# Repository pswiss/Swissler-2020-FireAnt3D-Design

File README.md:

# Swissler-2020-FireAnt3D-Design

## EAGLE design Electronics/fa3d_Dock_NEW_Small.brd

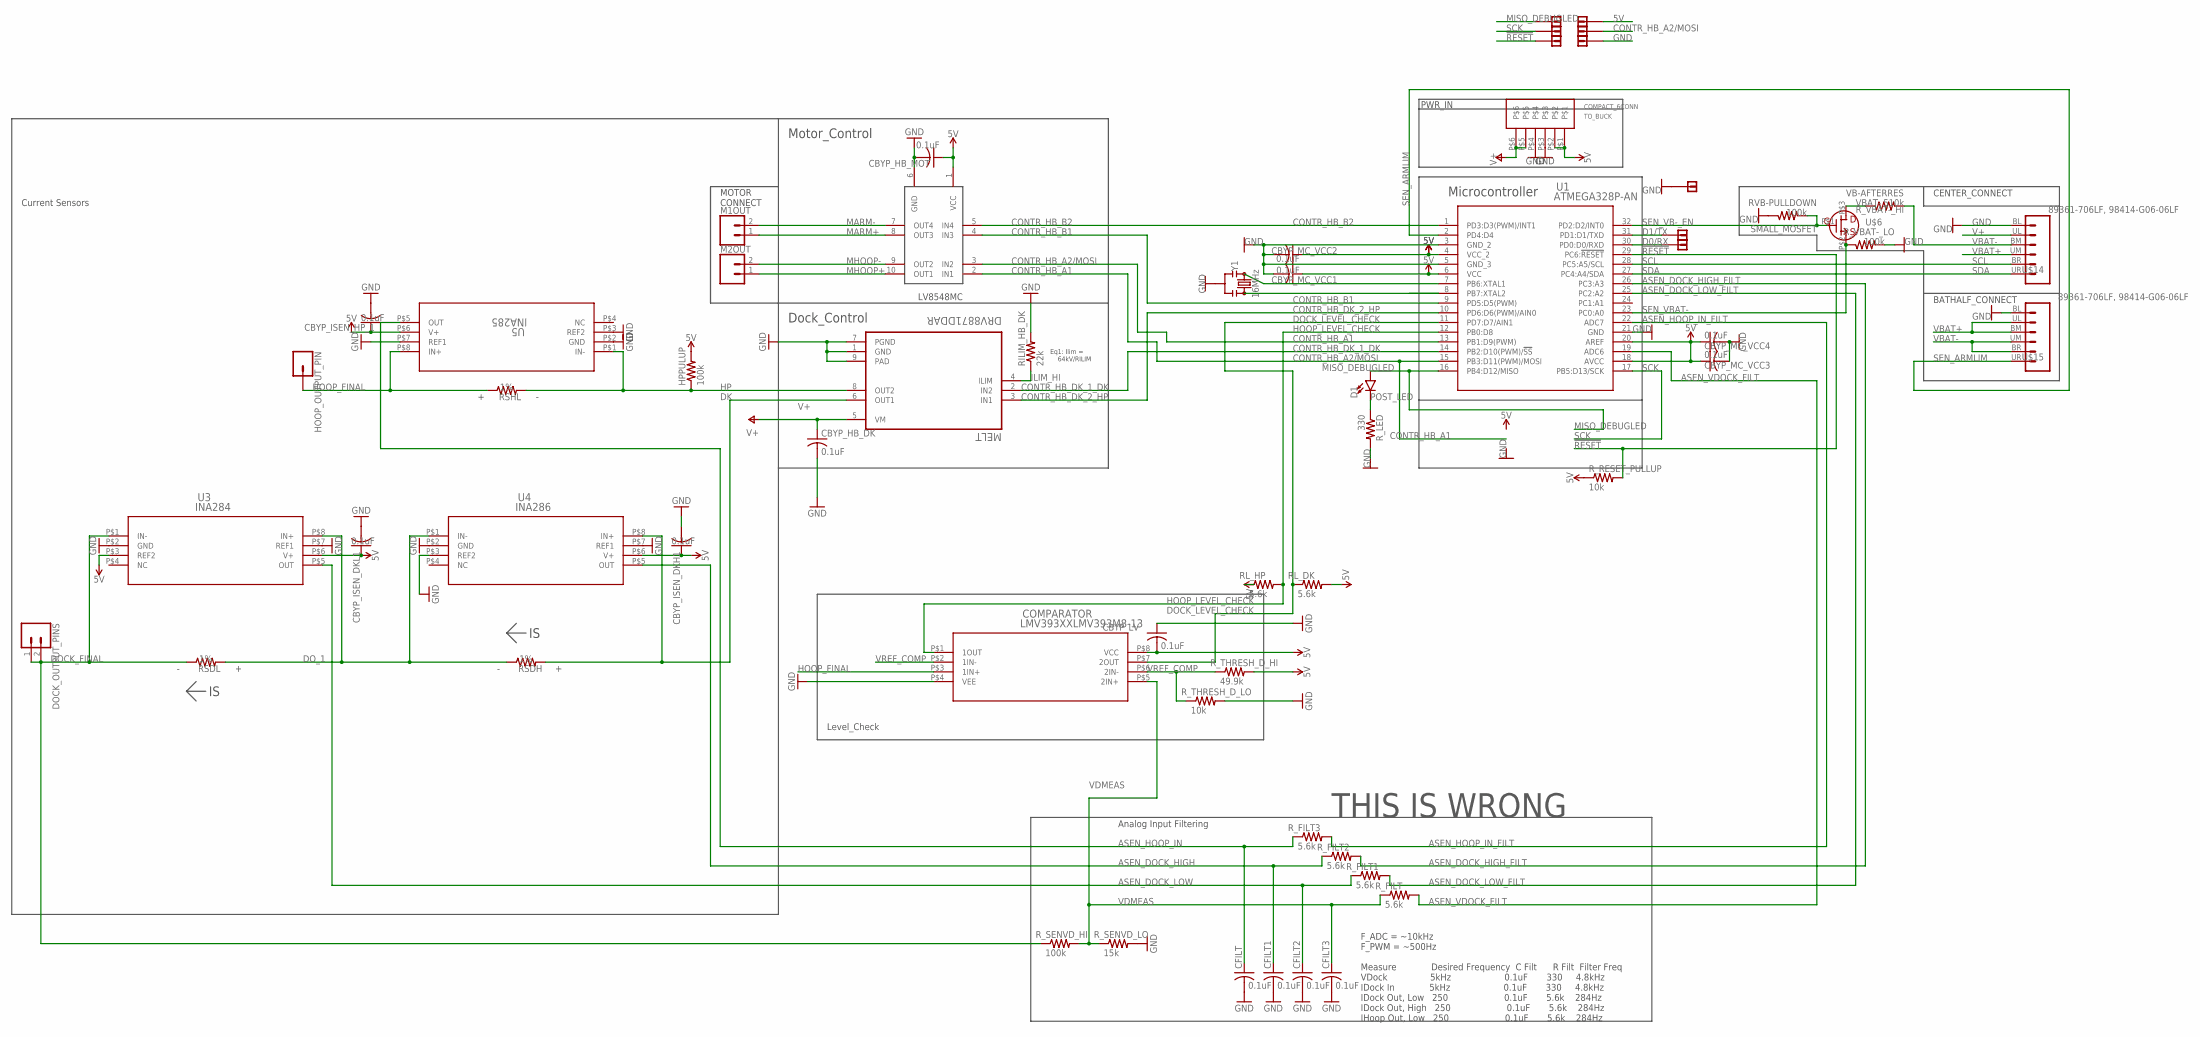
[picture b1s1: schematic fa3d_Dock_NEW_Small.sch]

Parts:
CBYP_HB_DK: 0.1uF; C0603; PARTNO CL10B104KB8NNNC
CBYP_HB_MOT: 0.1uF; C0402; PARTNO 885012105010
CBYP_ISEN_DKH1: 0.1uF; C0402; PARTNO 885012105010
CBYP_ISEN_DKL1: 0.1uF; C0402; PARTNO 885012105010
CBYP_ISEN_HP_1: 0.1uF; C0402; PARTNO 885012105010
CBYP_LV: 0.1uF; C0402; PARTNO 885012105010
CBYP_MC_VCC1, CBYP_MC_VCC2, CBYP_MC_VCC3, CBYP_MC_VCC4: 0.1uF; C0402; PARTNO 885012105010
CFILT, CFILT1, CFILT2, CFILT3: 0.1uF; C0402; PARTNO 885012105010
COMPARATOR: LMV393XXLMV393M8-13; MSOP-8; PARTNO LMV393M8-13
D1: LED0603; LED-0603; PARTNO SML-D12U1WT86
DOCK_OUTPUT_PINS: CONN_02; 1X02
HOOP_OUTPUT_PIN: CONN_01; 1X01
HPPULUP: 100k; R0402; PARTNO RMCF0402JT100K
M1OUT, M2OUT: CONN_02; 1X02
MELT: DRV8871DDAR; SOIC127P600X170-8N; PARTNO DRV8871DDAR
MOTOR: LV8548MC-AH; 10-SOP; PARTNO LV8548MC-AH
RILIM_HB_DK: 22k; R0603; PARTNO RMCF0402JT22K0
RL_DK: 5.6k; R0402; PARTNO CRGCQ0402F5K6
RL_HP: 5.6k; R0402; PARTNO CRGCQ0402F5K6
RSDH: 25m; R0603; PARTNO ERJ-3BWFR025V
RSDL: 25m; R0603; PARTNO ERJ-3BWFR025V
RSHL: 25m; R0603; PARTNO ERJ-3BWFR025V
RVB-PULLDOWN: 100k; R0402; PARTNO RMCF0402JT100K
R_FILT, R_FILT1, R_FILT2, R_FILT3: 5.6k; R0402; PARTNO CRGCQ0402F5K6
R_LED: 330; R0402; PARTNO RMCF0402JT330R
R_RESET_PULLUP: 10k; R0402; PARTNO RR0510P-103-D
R_SENVD_HI: 100k; R0402; PARTNO RMCF0402JT100K
R_SENVD_LO: 15k; R0402; PARTNO RMCF0402JT15K0
R_THRESH_D_HI: 49.9k; R0402; PARTNO RMCF0402FT49K9
R_THRESH_D_LO: 10k; R0402; PARTNO RR0510P-103-D
R_VBAT-_HI: 510k; R0402; PARTNO RMCF0402JT510K
R_VBAT-_LO: 100k; R0402; PARTNO RMCF0402JT100K
TO_BUCK: COMPACT_6CONN
U1: ATMEGA328P-AN; 32A; PARTNO ATMEGA328P-AUR
U3: INA284; 8-VSSOP; PARTNO INA284AIDGKR
U4: INA286; 8-VSSOP; PARTNO INA286AIDGKR
U5: INA285; 8-VSSOP; PARTNO INA285AIDGKR
U$1, U$2, U$3, U$4, U$5, U$7, U$8, U$9, U$10: SIMPLE_VIA_CONNECTION; SIMPLEVIA
U$6: SMALL_MOSFET; SOT-23; PARTNO BSS138
U$14, U$15: 89361-706LF, 98414-G06-06LF; 2X3_2MMPITCH; PARTNO 98414-G06-06LF
Y1: 16MHz; RESONATOR-SMD-3.2X1.3; PARTNO CSTNE16M0V530000R0

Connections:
5V: CBYP_HB_MOT.1, CBYP_ISEN_DKH1.1, CBYP_ISEN_DKL1.1, CBYP_ISEN_HP_1.1, CBYP_LV.2, CBYP_MC_VCC1.1, CBYP_MC_VCC2.1, CBYP_MC_VCC3.1, CBYP_MC_VCC4.1, COMPARATOR.P$8 (VCC), HPPULUP.2, MOTOR.1 (VCC), RL_DK.2, RL_HP.1, R_RESET_PULLUP.1, R_THRESH_D_HI.2, TO_BUCK.P$1, TO_BUCK.P$2, U1.4 (VCC_2), U1.6 (VCC), U1.18 (AVCC), U1.20 (AREF), U3.P$3 (REF2), U3.P$6 (V+), U4.P$6 (V+), U5.P$6 (V+), U$10.P$1
!RESET: R_RESET_PULLUP.2, U1.29 (PC6:!RESET), U$7.P$1
ASEN_DOCK_HIGH: CFILT1.1, R_FILT2.1, U4.P$5 (OUT)
ASEN_DOCK_HIGH_FILT: R_FILT2.2, U1.26 (PC3:A3)
ASEN_DOCK_LOW: CFILT2.1, R_FILT1.1, U3.P$5 (OUT)
ASEN_DOCK_LOW_FILT: R_FILT1.2, U1.25 (PC2:A2)
ASEN_HOOP_IN: CFILT.1, R_FILT3.1, U5.P$5 (OUT)
ASEN_HOOP_IN_FILT: R_FILT3.2, U1.22 (ADC7)
ASEN_VDOCK_FILT: R_FILT.2, U1.19 (ADC6)
CONTR_HB_A1: MOTOR.2 (IN1), U1.15 (PB3:D11(PWM)/MOSI)
CONTR_HB_A2/MOSI: MOTOR.3 (IN2), U1.13 (PB1:D9(PWM)), U$9.P$1
CONTR_HB_B1: MOTOR.4 (IN3), U1.9 (PD5:D5(PWM))
CONTR_HB_B2: MOTOR.5 (IN4), U1.1 (PD3:D3(PWM)/INT1)
CONTR_HB_DK_1_DK: MELT.2 (IN2), U1.14 (PB2:D10(PWM)/!SS)
CONTR_HB_DK_2_HP: MELT.3 (IN1), U1.10 (PD6:D6(PWM)/AIN0)
D0/RX: U1.30 (PD0:D0/RXD), U$5.P$1
D1/TX: U1.31 (PD1:D1/TXD), U$4.P$1
DK: MELT.6 (OUT1), RSDH.2, U4.P$8 (IN+)
DOCK_FINAL: DOCK_OUTPUT_PINS.1, DOCK_OUTPUT_PINS.2, RSDL.1, R_SENVD_HI.1, U3.P$1 (IN-)
DOCK_LEVEL_CHECK: COMPARATOR.P$7 (2OUT), RL_DK.1, U1.11 (PD7:D7/AIN1)
DO_1: RSDH.1, RSDL.2, U3.P$8 (IN+), U4.P$1 (IN-)
GND: CBYP_HB_DK.2, CBYP_HB_MOT.2, CBYP_ISEN_DKH1.2, CBYP_ISEN_DKL1.2, CBYP_ISEN_HP_1.2, CBYP_LV.1, CBYP_MC_VCC1.2, CBYP_MC_VCC2.2, CBYP_MC_VCC3.2, CBYP_MC_VCC4.2, CFILT.2, CFILT1.2, CFILT2.2, CFILT3.2, COMPARATOR.P$4 (VEE), MELT.1 (GND), MELT.7 (PGND), MELT.9 (PAD), MOTOR.6 (GND), RILIM_HB_DK.2, RVB-PULLDOWN.1, R_LED.2, R_SENVD_LO.2, R_THRESH_D_LO.2, R_VBAT-_LO.2, TO_BUCK.P$3, TO_BUCK.P$4, U1.3 (GND_2), U1.5 (GND_3), U1.21 (GND), U3.P$2 (GND), U3.P$7 (REF1), U4.P$2 (GND), U4.P$3 (REF2), U4.P$7 (REF1), U5.P$2 (GND), U5.P$3 (REF2), U5.P$7 (REF1), U$1.P$1, U$8.P$1, U$14.BL (1), U$15.BL (1), Y1.2
HOOP_FINAL: COMPARATOR.P$3 (1IN+), HOOP_OUTPUT_PIN.1, RSHL.1, U5.P$8 (IN+)
HOOP_LEVEL_CHECK: COMPARATOR.P$1 (1OUT), RL_HP.2, U1.12 (PB0:D8)
HP: HPPULUP.1, MELT.8 (OUT2), RSHL.2, U5.P$1 (IN-)
ILIM_HI: MELT.4 (ILIM), RILIM_HB_DK.1
MARM+: M1OUT.1, MOTOR.8 (OUT3)
MARM-: M1OUT.2, MOTOR.7 (OUT4)
MHOOP+: M2OUT.1, MOTOR.10 (OUT1)
MHOOP-: M2OUT.2, MOTOR.9 (OUT2)
MISO_DEBUGLED: D1.A, U1.16 (PB4:D12/MISO), U$2.P$1
POST_LED: D1.C, R_LED.1
SCK: U1.17 (PB5:D13/SCK), U$3.P$1
SCL: U1.28 (PC5:A5/SCL), U$14.BR (5)
SDA: U1.27 (PC4:A4/SDA), U$14.UR (6)
SEN_ARMLIM: U1.2 (PD4:D4), U$15.UR (6)
SEN_VB-_EN: RVB-PULLDOWN.2, U1.32 (PD2:D2/INT0), U$6.P$1 (G)
SEN_VBAT-: R_VBAT-_LO.1, U1.23 (PC0:A0), U$6.P$2 (S)
V+: CBYP_HB_DK.1, MELT.5 (VM), TO_BUCK.P$5, TO_BUCK.P$6, U$14.UL (2)
VB-AFTERRES: R_VBAT-_HI.1, U$6.P$3 (D)
VBAT+: U$14.UM (4), U$15.BM (3), U$15.UL (2)
VBAT-: R_VBAT-_HI.2, U$14.BM (3), U$15.BR (5), U$15.UM (4)
VDMEAS: CFILT3.1, COMPARATOR.P$5 (2IN+), R_FILT.1, R_SENVD_HI.2, R_SENVD_LO.1
VREF_COMP: COMPARATOR.P$2 (1IN-), COMPARATOR.P$6 (2IN-), R_THRESH_D_HI.1, R_THRESH_D_LO.1
XTAL1/TOSC1: U1.7 (PB6:XTAL1), Y1.1
XTAL2/TOSC2: U1.8 (PB7:XTAL2), Y1.3

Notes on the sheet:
Microcontroller
PWR_IN
CENTER_CONNECT
BATHALF_CONNECT
Motor_Control
Dock_Control
Eq1: Ilim = 64kV/RILIM
MOTOR CONNECT
Level_Check
Analog Input Filtering
F_ADC = ~10kHz F_PWM = ~500Hz Measure Desired Frequency C Filt R Filt Filter Freq VDock 5kHz 0.1uF 330 4.8kHz IDock In 5kHz 0.1uF 330 4.8kHz IDock Out, Low 250 0.1uF 5.6k 284Hz IDock Out, High 250 0.1uF 5.6k 284Hz IHoop Out, Low 250 0.1uF 5.6k 284Hz
Current Sensors
THIS IS WRONG

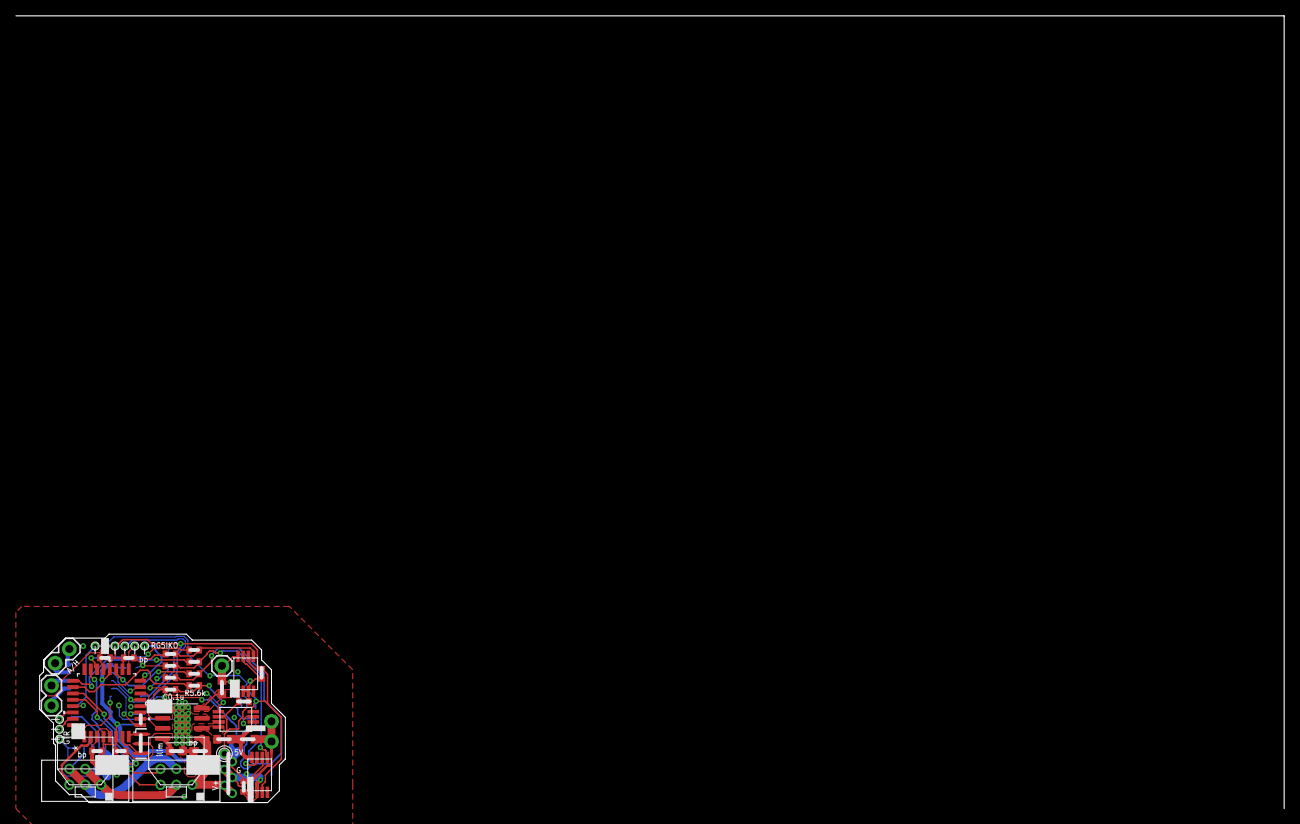
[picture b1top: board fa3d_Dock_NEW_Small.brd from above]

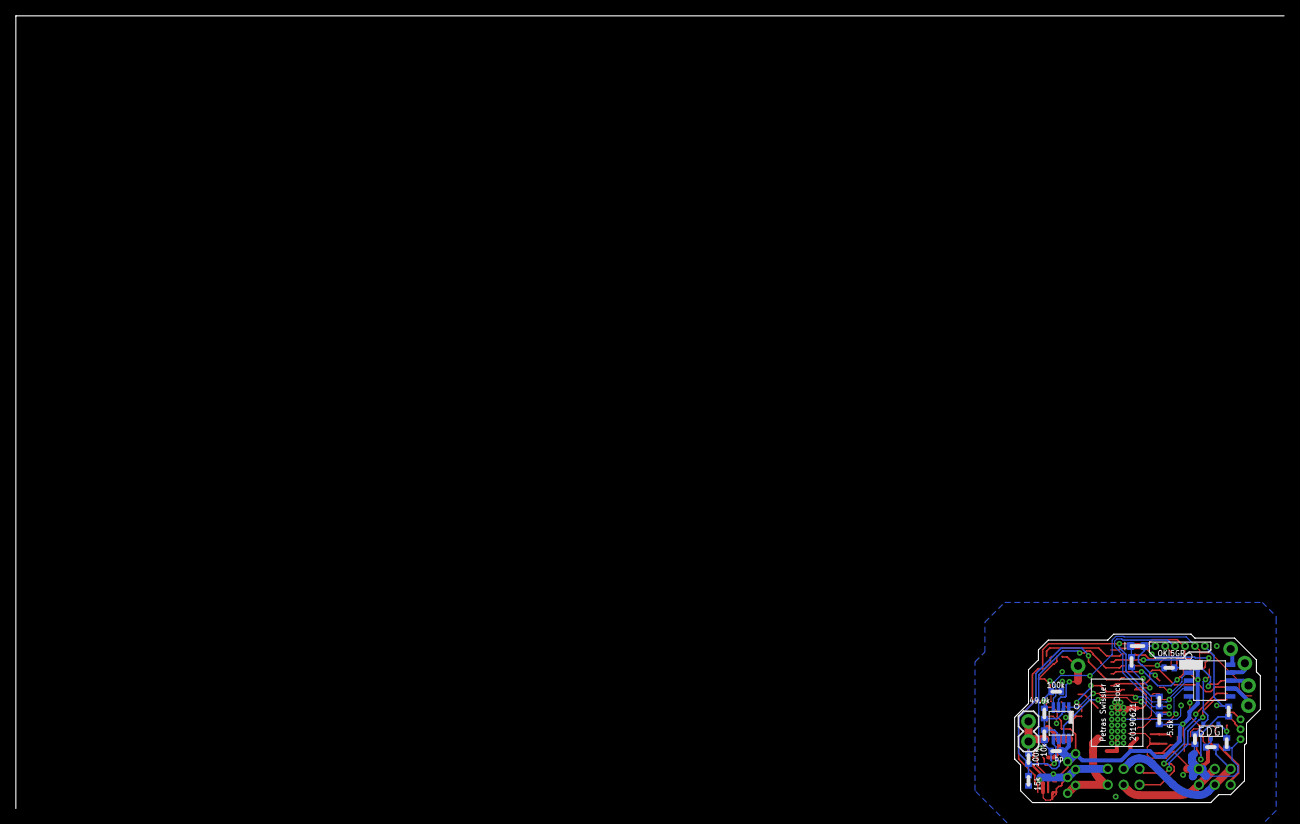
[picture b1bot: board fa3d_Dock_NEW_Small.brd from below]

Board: 2 copper layers, 160.0 x 100.0 mm, 60 parts (19 on the bottom side), 46 nets.

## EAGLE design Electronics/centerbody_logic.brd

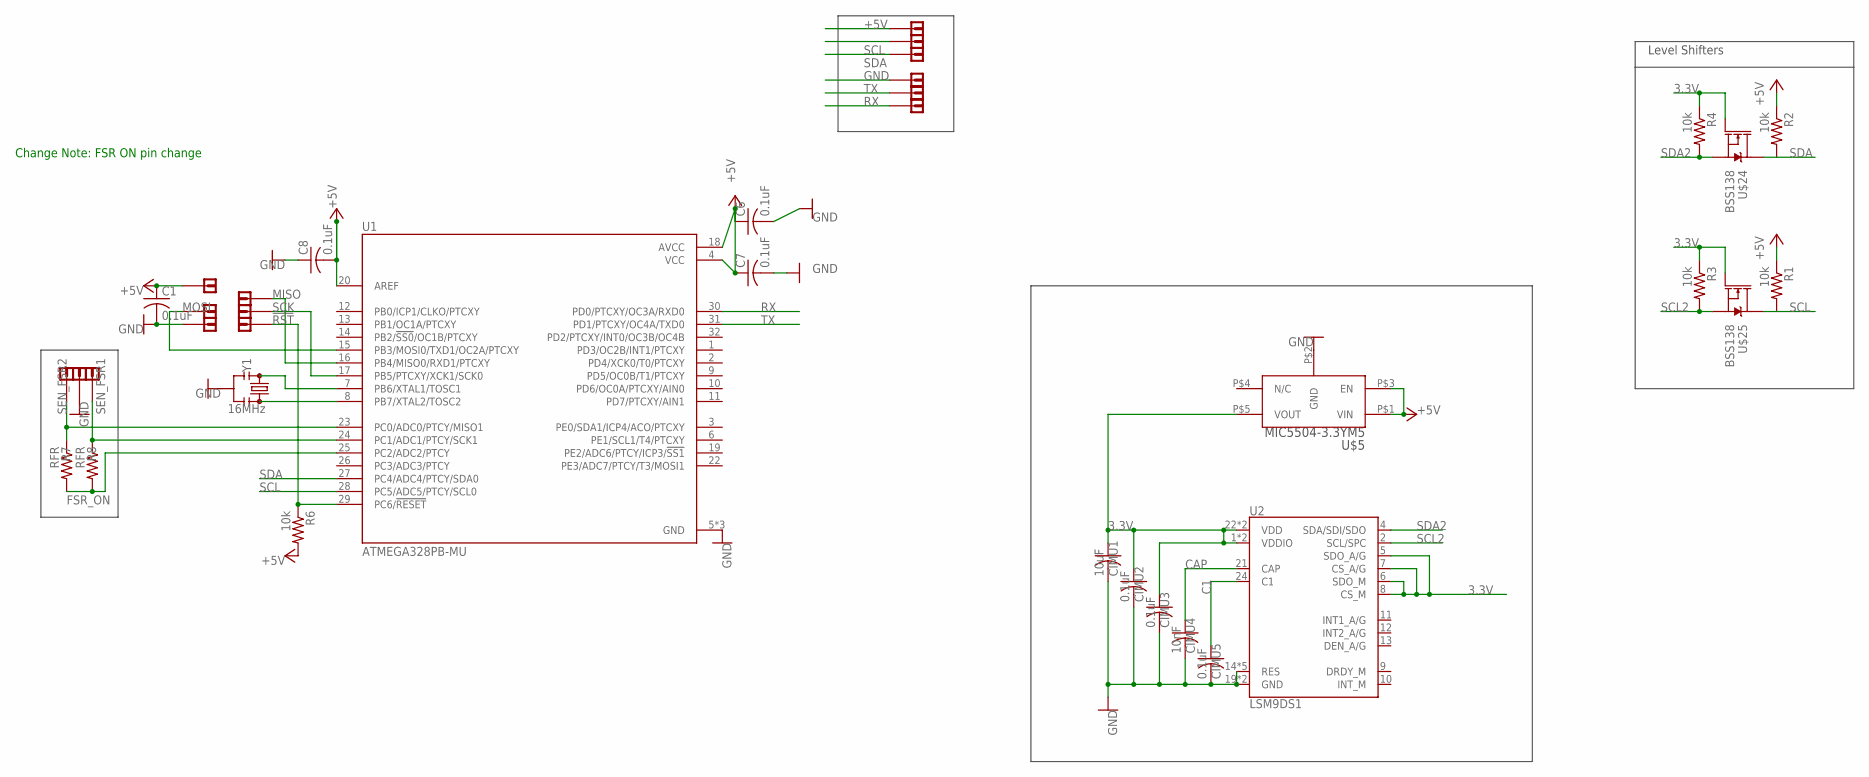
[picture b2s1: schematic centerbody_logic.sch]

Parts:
C1, C6, C7, C8: 0.1uF; C0402; PARTNO 885012105010
CIMU1: 10uF; C0402; PARTNO GRM155R60G106ME44D
CIMU2, CIMU3, CIMU5: 0.1uF; C0402; PARTNO 885012105010
CIMU4: 10nF; C0402; PARTNO CL05B103KB5NNNC
R1, R2, R3, R4, R6: 10k; R0402; PARTNO RR0510P-103-D
R7, R8: RFR; R0402; PARTNO CRGCQ0402F5K6
U1: ATMEGA328PB-MU; QFN50P500X500X90-33N; PARTNO ATMEGA328PB-MUR
U2: LSM9DS1; LGA24-8X4; PARTNO LSM9DS1TR
U$1, U$3, U$4, U$6, U$7, U$8, U$9, U$10, U$11, U$12, U$13, U$14, U$15, U$26, U$27: SIMPLE_VIA_CONNECTION; SIMPLEVIA
U$5: MIC5504-3.3YM5; SOT23; PARTNO MIC5504-3.3YM5-TR
U$24, U$25: BSS138; SOT-23; PARTNO BSS138
Y1: 16MHz; RESONATOR-SMD-3.2X1.3; PARTNO CSTNE16M0V530000R0

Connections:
3.3V: CIMU1.1, CIMU2.1, CIMU3.1, R3.1, R4.1, U2.1 (VDDIO), U2.3 (VDDIO), U2.5 (SDO_A/G), U2.6 (SDO_M), U2.7 (CS_A/G), U2.8 (CS_M), U2.22 (VDD), U2.23 (VDD), U$5.P$5 (VOUT), U$24.P$1 (G), U$25.P$1 (G)
!RST: R6.1, U1.29 (PC6/!RESET!), U$13.P$1
+5V: C1.1, C6.1, C7.1, C8.2, R1.1, R2.1, R6.2, U1.4 (VCC), U1.18 (AVCC), U1.20 (AREF), U$5.P$1 (VIN), U$5.P$3 (EN), U$7.P$1, U$10.P$1
C1: CIMU5.1, U2.24 (C1)
CAP: CIMU4.1, U2.21 (CAP)
FSR_ON: R7.2, R8.2, U1.25 (PC2/ADC2/PTCY)
GND: C1.2, C6.2, C7.2, C8.1, CIMU1.2, CIMU2.2, CIMU3.2, CIMU4.2, CIMU5.2, U1.5 (GND), U1.21 (GND), U1.33 (GND), U2.14 (RES), U2.15 (RES), U2.16 (RES), U2.17 (RES), U2.18 (RES), U2.19 (GND), U2.20 (GND), U$3.P$1, U$5.P$2 (GND), U$6.P$1, U$12.P$1, Y1.2
MISO: U1.16 (PB4/MISO0/RXD1/PTCXY), U$15.P$1
MOSI: U1.15 (PB3/MOSI0/TXD1/OC2A/PTCXY), U$11.P$1
unnamed: U1.8 (PB7/XTAL2/TOSC2), Y1.3
unnamed: U1.7 (PB6/XTAL1/TOSC1), Y1.1
RX: U1.30 (PD0/PTCXY/OC3A/RXD0), U$27.P$1
SCK: U1.17 (PB5/PTCXY/XCK1/SCK0), U$14.P$1
SCL: R1.2, U1.28 (PC5/ADC5/PTCY/SCL0), U$9.P$1, U$25.P$3 (D)
SCL2: R3.2, U2.2 (SCL/SPC), U$25.P$2 (S)
SDA: R2.2, U1.27 (PC4/ADC4/PTCY/SDA0), U$4.P$1, U$24.P$3 (D)
SDA2: R4.2, U2.4 (SDA/SDI/SDO), U$24.P$2 (S)
SEN_FSR1: R8.1, U1.24 (PC1/ADC1/PTCY/SCK1), U$8.P$1
SEN_FSR2: R7.1, U1.23 (PC0/ADC0/PTCY/MISO1), U$1.P$1
TX: U1.31 (PD1/PTCXY/OC4A/TXD0), U$26.P$1

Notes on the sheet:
Level Shifters
Change Note: FSR ON pin change

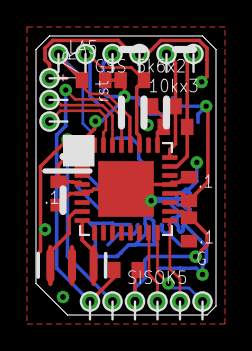
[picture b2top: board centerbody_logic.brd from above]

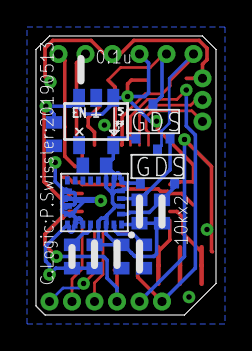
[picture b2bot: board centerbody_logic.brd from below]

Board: 2 copper layers, 10.0 x 15.5 mm, 37 parts (12 on the bottom side), 20 nets.

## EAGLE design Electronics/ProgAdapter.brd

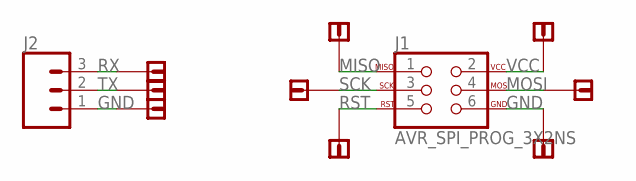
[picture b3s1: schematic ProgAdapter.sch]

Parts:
J1: AVR_SPI_PROG_3X2NS; 2X3-NS
J2: CONN_03; 1X03
U$1, U$2, U$3, U$4, U$5, U$6, U$7, U$8, U$9: SIMPLE_VIA_CONNECTION; SIMPLEVIA

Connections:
GND: J1.6, J2.1, U$4.P$1, U$9.P$1
MISO: J1.1, U$1.P$1
MOSI: J1.4, U$5.P$1
RST: J1.5, U$3.P$1
RX: J2.3, U$7.P$1
SCK: J1.3, U$2.P$1
TX: J2.2, U$8.P$1
VCC: J1.2, U$6.P$1

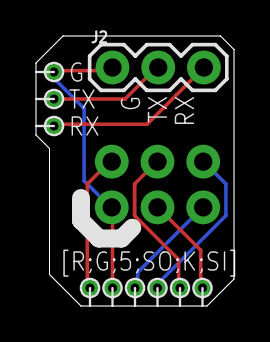
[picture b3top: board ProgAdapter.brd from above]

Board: 2 copper layers, 11.0 x 15.0 mm, 11 parts (0 on the bottom side), 8 nets.

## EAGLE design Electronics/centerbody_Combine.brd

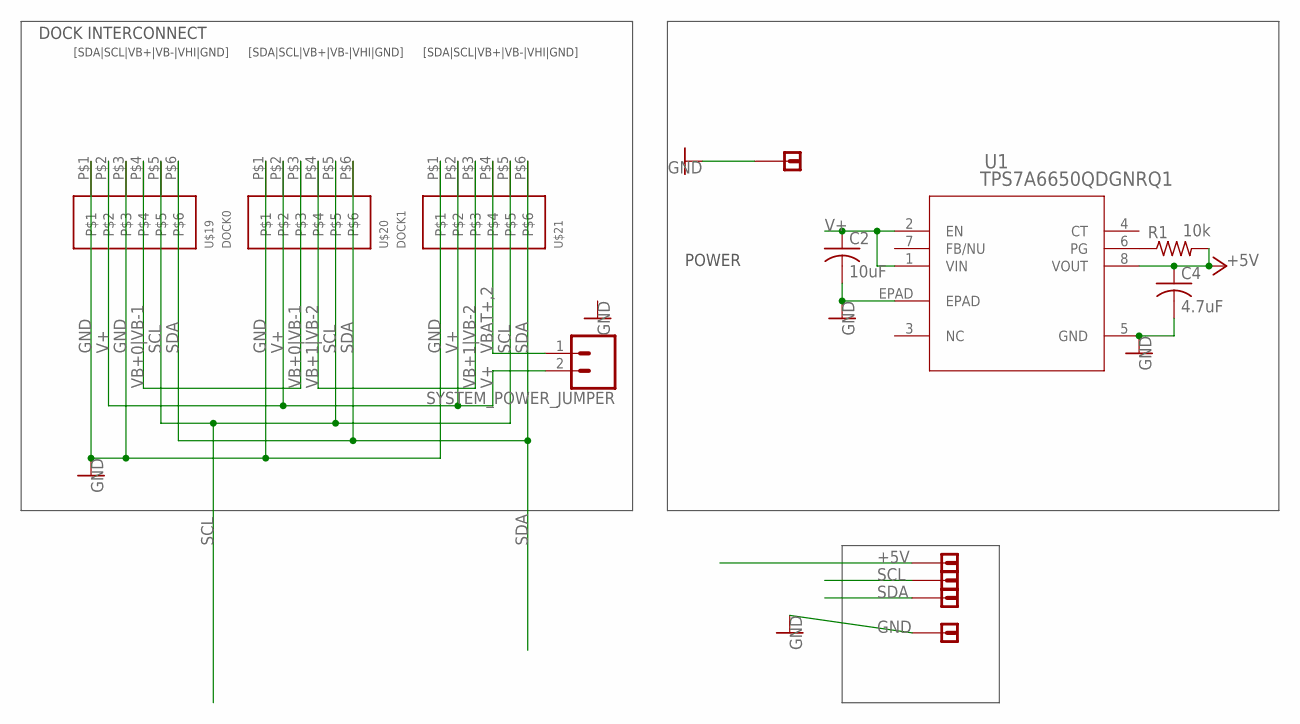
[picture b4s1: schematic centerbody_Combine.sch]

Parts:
C2: 10uF; C1206
C4: 4.7uF; C0402
R1: 10k; R0402
SYSTEM_POWER_JUMPER: CONN_02; 1X02
U1: TPS7A6650QDGNRQ1; DGN8_1P57X1P89
U$1, U$3, U$4, U$7, U$9: SIMPLE_VIA_CONNECTION; SIMPLEVIA
U$19: DOCK0; COMPACT_6CONN_STRAIGHT
U$20: DOCK1; COMPACT_6CONN_STRAIGHT
U$21: DOCK_2; COMPACT_6CONN_STRAIGHT

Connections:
+5V: C4.1, R1.2, U1.8 (VOUT), U$7.P$1
GND: C2.2, C4.2, U1.5 (GND), U1.EPAD, U$1.P$1, U$3.P$1, U$19.P$1, U$19.P$3, U$20.P$1, U$21.P$1
unnamed: R1.1, U1.6 (PG)
SCL: U$9.P$1, U$19.P$5, U$20.P$5, U$21.P$5
SDA: U$4.P$1, U$19.P$6, U$20.P$6, U$21.P$6
V+: C2.1, SYSTEM_POWER_JUMPER.2, U1.1 (VIN), U1.2 (EN), U$19.P$2, U$20.P$2, U$21.P$2
VB+0|VB-1: U$19.P$4, U$20.P$3
VB+1|VB-2: U$20.P$4, U$21.P$3
VBAT+,2: SYSTEM_POWER_JUMPER.1, U$21.P$4

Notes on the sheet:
[SDA|SCL|VB+|VB-|VHI|GND]
DOCK INTERCONNECT
POWER

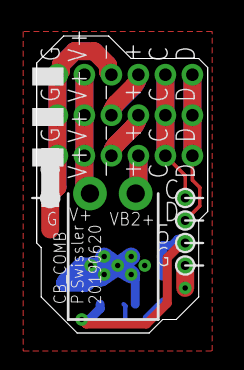
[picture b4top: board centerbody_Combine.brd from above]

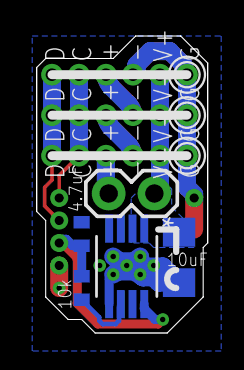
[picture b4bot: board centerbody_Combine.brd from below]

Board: 2 copper layers, 9.5 x 16.5 mm, 13 parts (8 on the bottom side), 9 nets.

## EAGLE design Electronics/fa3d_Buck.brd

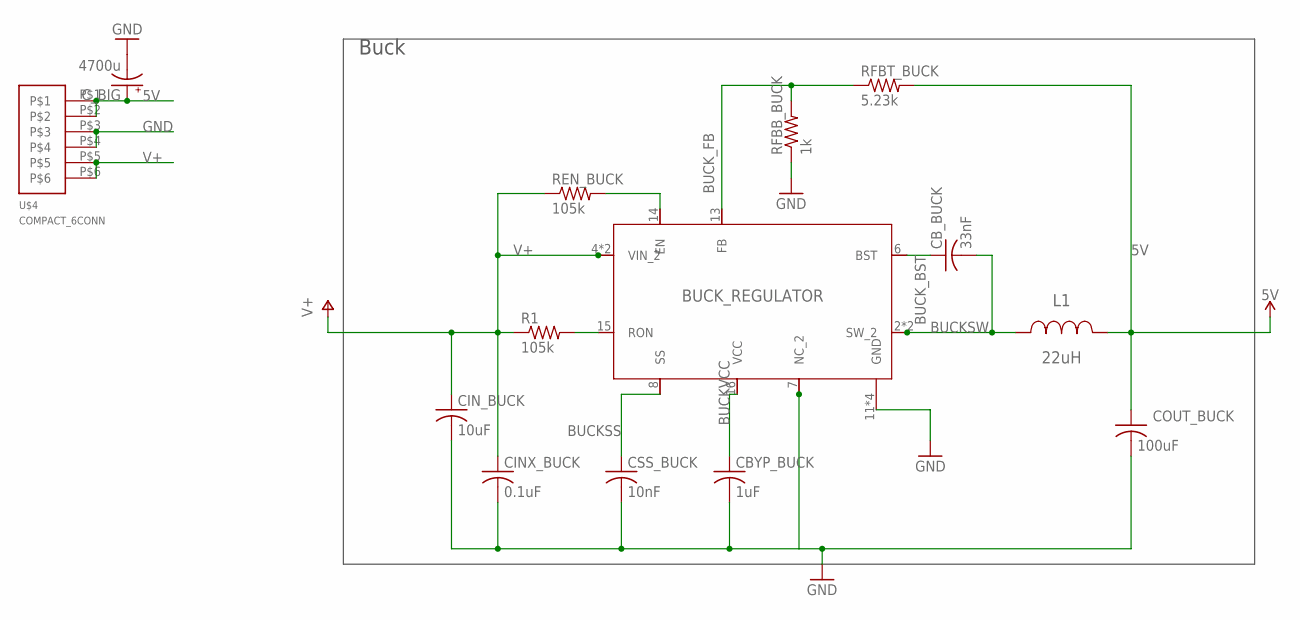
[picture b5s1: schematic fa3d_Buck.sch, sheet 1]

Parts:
BUCK_REGULATOR: BUCK; MXA20A; PARTNO LM3102MH/NOPB
CBYP_BUCK: 1uF; C0603; PARTNO CL10A105KB8NNNC
CB_BUCK: 33nF; C0603; PARTNO 885012206092
CINX_BUCK: 0.1uF; C0603; PARTNO CL10B104KB8NNNC
CIN_BUCK: 10uF; C1206; PARTNO GRM188R6YA106MA73D
COUT_BUCK: 100uF; C1206; PARTNO CL31A107MQHNNNE
CSS_BUCK: 10nF; C0603; PARTNO 885012206089
C_BIG: 4700u; TT5D11; PARTNO UVR0J472MHD
L1: 22uH; SDR1307; PARTNO SDR1307-220ML
R1: 105k; R0603; PARTNO RMCF0603FT105K
REN_BUCK: 105k; R0603; PARTNO RMCF0603FT105K
RFBB_BUCK: 1k; R0603; PARTNO RMCF0603JJ1K00
RFBT_BUCK: 5.23k; R0603; PARTNO RMCF0603FT5K23
U$4: COMPACT_6CONN

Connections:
5V: COUT_BUCK.1, C_BIG.+, L1.2, RFBT_BUCK.2, U$4.P$1, U$4.P$2
BUCKEN: BUCK_REGULATOR.14 (EN), REN_BUCK.2
BUCKRON: BUCK_REGULATOR.15 (RON), R1.2
BUCKSS: BUCK_REGULATOR.8 (SS), CSS_BUCK.1
BUCKSW: BUCK_REGULATOR.2 (SW_2), BUCK_REGULATOR.3 (SW_2), CB_BUCK.2, L1.1
BUCKVCC: BUCK_REGULATOR.16 (VCC), CBYP_BUCK.1
BUCK_BST: BUCK_REGULATOR.6 (BST), CB_BUCK.1
BUCK_FB: BUCK_REGULATOR.13 (FB), RFBB_BUCK.2, RFBT_BUCK.1
GND: BUCK_REGULATOR.7 (NC_2), BUCK_REGULATOR.11 (GND), BUCK_REGULATOR.17 (GND), BUCK_REGULATOR.18 (GND), BUCK_REGULATOR.21 (GND), CBYP_BUCK.2, CINX_BUCK.2, CIN_BUCK.2, COUT_BUCK.2, CSS_BUCK.2, C_BIG.-, RFBB_BUCK.1, U$4.P$3, U$4.P$4
V+: BUCK_REGULATOR.4 (VIN_2), BUCK_REGULATOR.5 (VIN_2), CINX_BUCK.1, CIN_BUCK.1, R1.1, REN_BUCK.1, U$4.P$5, U$4.P$6

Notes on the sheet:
Buck

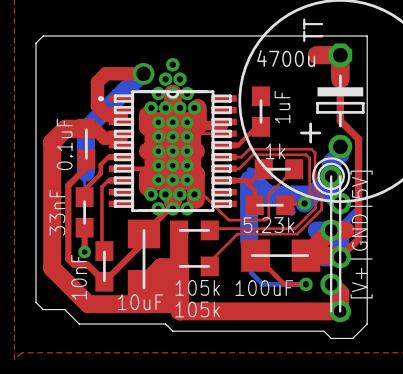
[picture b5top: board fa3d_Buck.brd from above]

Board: 2 copper layers, 18.4 x 16.8 mm, 14 parts (1 on the bottom side), 10 nets.

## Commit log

2020-07-23 Added design materials and code

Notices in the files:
parts and their libraries:
SparkFun-Connectors: Licensing: Creative Commons ShareAlike 4.0 International - https://creativecommons.org/licenses/by-sa/4.0
